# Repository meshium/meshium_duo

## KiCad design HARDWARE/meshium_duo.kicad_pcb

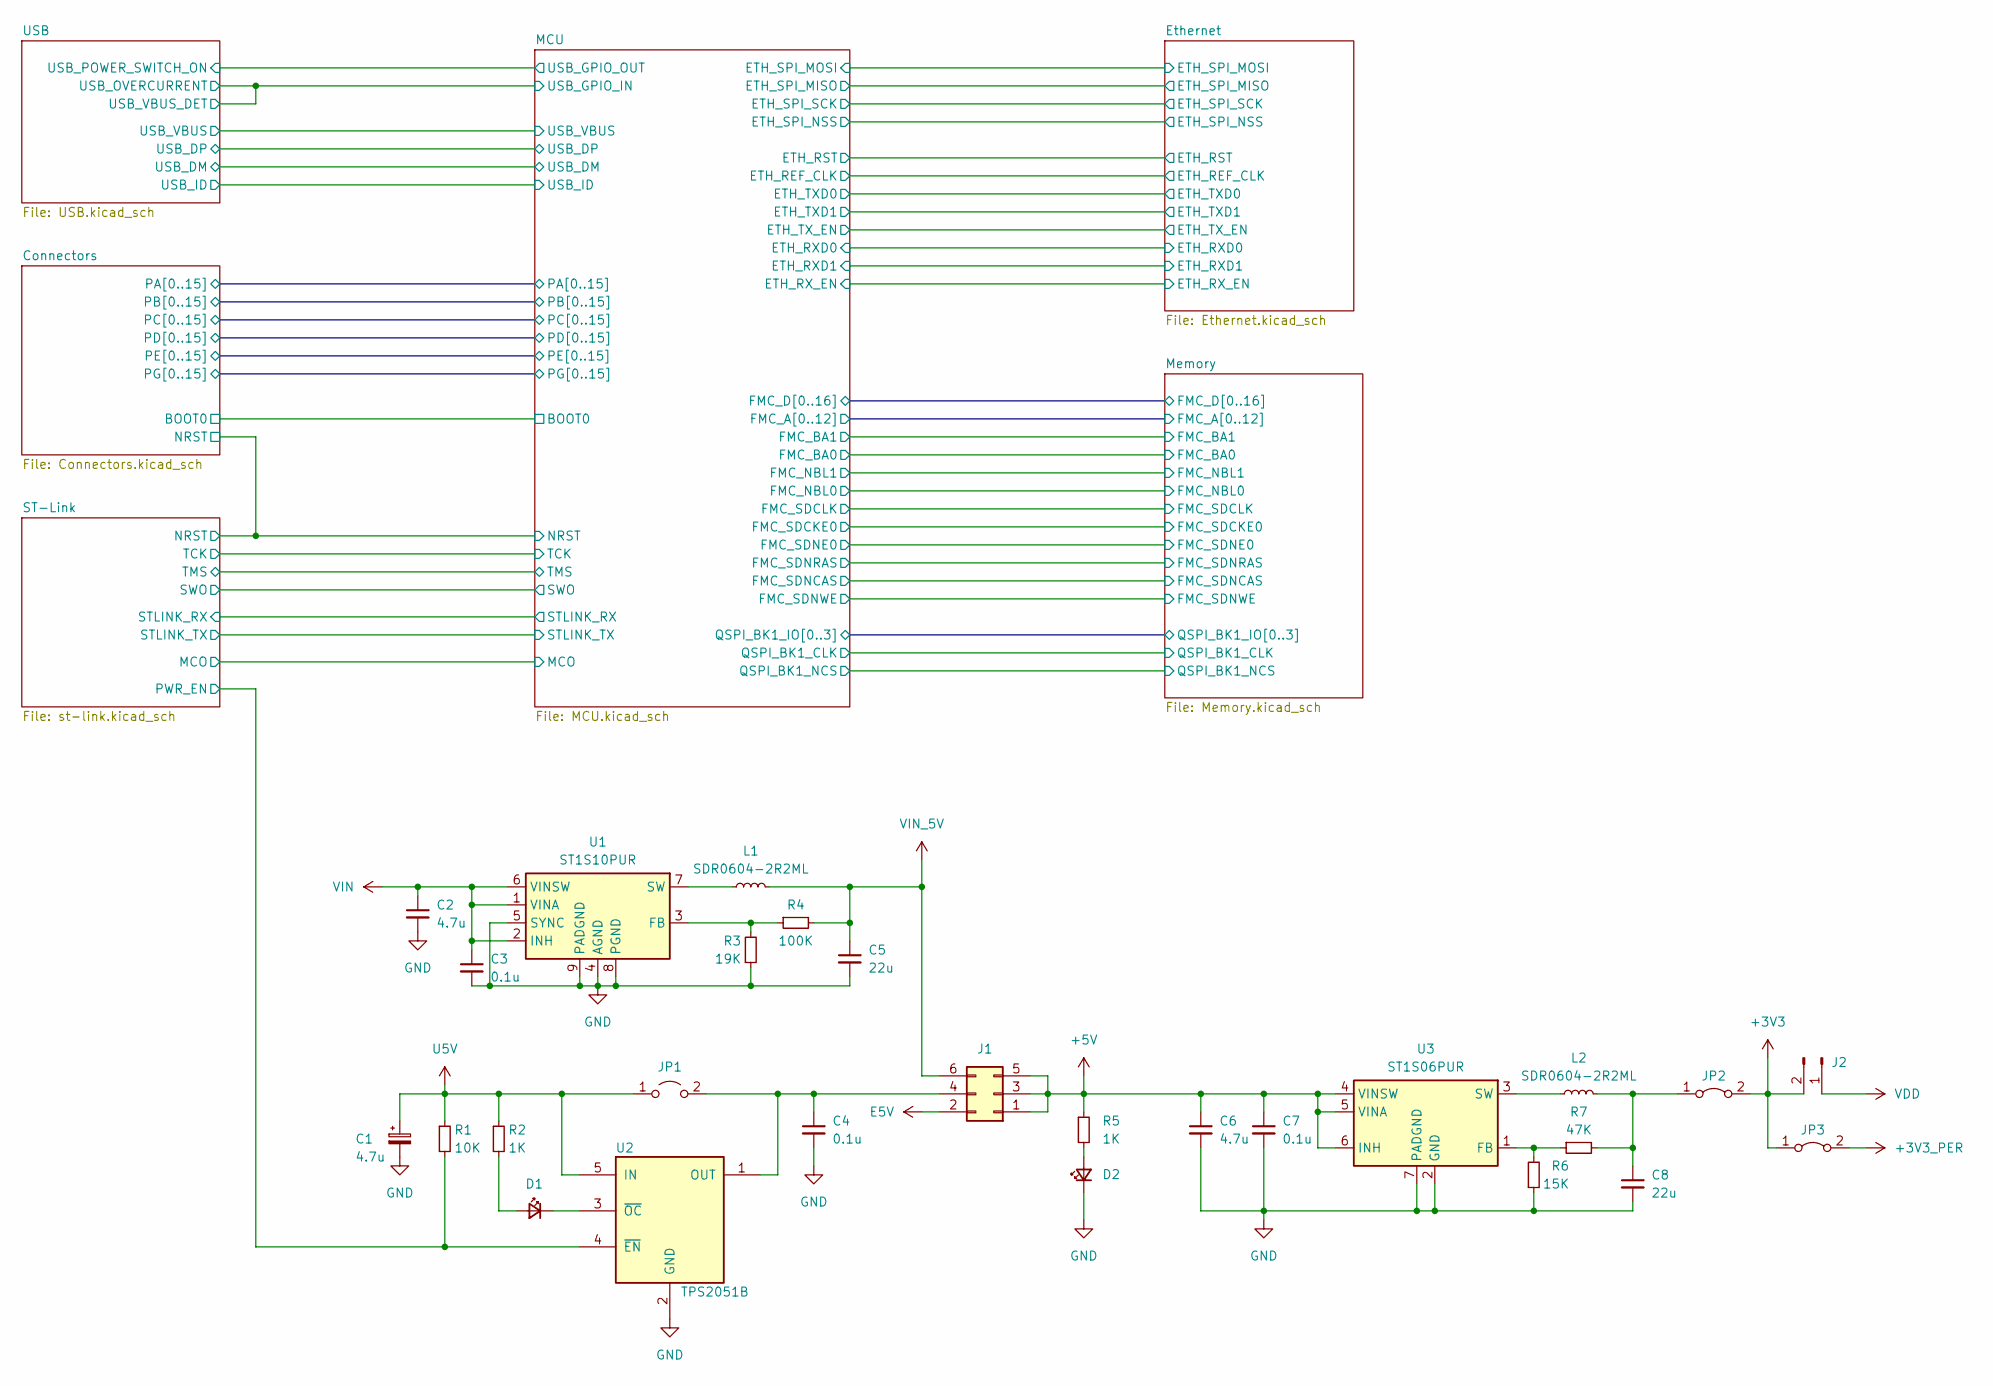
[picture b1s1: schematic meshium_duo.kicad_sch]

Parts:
C1: 4.7u; CP_EIA-6032-28_Kemet-C
C2, C6: 4.7u; C_0603_1608Metric
C3, C4, C7: 0.1u; C_0603_1608Metric
C5, C8: 22u; C_0805_2012Metric
D1, D2: LED_Small; LED_0603_1608Metric
J1: Conn_02x03_Odd_Even; PinHeader_2x03_P2.54mm_Vertical
J2: Conn_01x02_Pin; PinHeader_1x02_P2.54mm_Vertical
JP1: Jumper_2_Open; SolderJumper-2_P1.3mm_Open_TrianglePad1.0x1.5mm
JP2, JP3: Jumper_2_Bridged; SolderJumper-2_P1.3mm_Open_TrianglePad1.0x1.5mm
L1, L2: SDR0604-2R2ML; L_Bourns-SRN0604
R1: 10K; R_0603_1608Metric
R2, R5: 1K; R_0603_1608Metric
R3: 19K; R_0603_1608Metric
R4: 100K; R_0603_1608Metric
R6: 15K; R_0603_1608Metric
R7: 47K; R_0603_1608Metric
U1: ST1S10PUR; DFN-8-1EP_4x4mm_P0.8mm_EP2.5x3.6mm
U2: TPS2051B; SOT-23-5
U3: ST1S06PUR; DFN-6-1EP_3x3mm_P0.95mm_EP1.7x2.6mm

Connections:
+3V3_PER: JP3.2 (B); also elsewhere on the board
+5V: C6.1, C7.1, J1.1, J1.3, J1.5, R5.1, U3.4 (VINSW), U3.5 (VINA), U3.6 (INH); also elsewhere on the board
/ST-Link/PWR_EN: R1.2, U2.4 (~EN); also elsewhere on the board
E5V: J1.2; also elsewhere on the board
unnamed: D1.2 (A), R2.2
unnamed: D1.1 (K), U2.3 (~OC)
unnamed: D2.2 (A), R5.2
unnamed: C4.1, J1.4, JP1.2 (B), U2.1 (OUT)
unnamed: C8.1, JP2.1 (A), L2.2, R7.2
unnamed: R3.2, R4.1, U1.3 (FB)
unnamed: L1.1, U1.7 (SW)
unnamed: R6.2, R7.1, U3.1 (FB)
unnamed: L2.1, U3.3 (SW)
U5V: C1.1, JP1.1 (A), R1.1, R2.1, U2.5 (IN); also elsewhere on the board
VDD: J2.1; also elsewhere on the board
VIN: C2.1, C3.1, U1.1 (VINA), U1.2 (INH), U1.6 (VINSW); also elsewhere on the board
VIN_5V: C5.1, J1.6, L1.2, R4.2; also elsewhere on the board

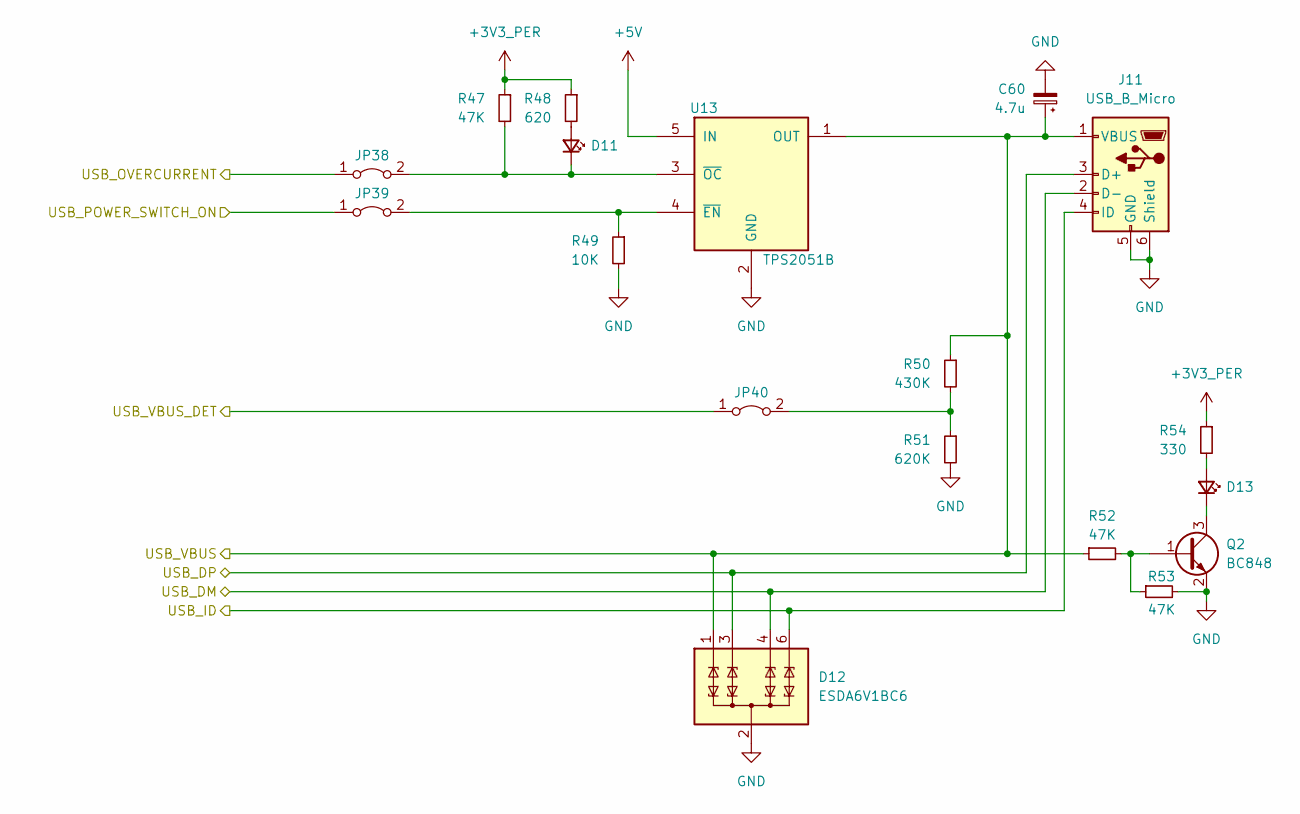
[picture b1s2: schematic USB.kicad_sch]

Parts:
C60: 4.7u; CP_EIA-6032-28_Kemet-C
D11, D13: LED_Small; LED_0603_1608Metric
D12: ESDA6V1BC6; SOT-23-6
J11: USB_B_Micro; USB_Micro-B_CUZD188-CB1Z
JP38, JP39, JP40: Jumper_2_Bridged; SolderJumper-2_P1.3mm_Open_TrianglePad1.0x1.5mm
Q2: BC848; SOT-23
R47, R52, R53: 47K; R_0603_1608Metric
R48: 620; R_0603_1608Metric
R49: 10K; R_0603_1608Metric
R50: 430K; R_0603_1608Metric
R51: 620K; R_0603_1608Metric
R54: 330; R_0603_1608Metric
U13: TPS2051B; SOT-23-5

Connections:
+3V3_PER: R47.1, R48.1, R54.1; also elsewhere on the board
+5V: U13.5 (IN); also elsewhere on the board
/Connectors/PG6: JP39.1 (A); also elsewhere on the board
/MCU/USB_DM: D12.4 (TVS3), J11.2 (D-); also elsewhere on the board
/MCU/USB_DP: D12.3 (TVS2), J11.3 (D+); also elsewhere on the board
/MCU/USB_GPIO_IN: JP38.1 (A), JP40.1 (A); also elsewhere on the board
/MCU/USB_ID: D12.6 (TVS4), J11.4 (ID); also elsewhere on the board
/MCU/USB_VBUS: C60.1, D12.1 (TVS1), J11.1 (VBUS), R50.1, R52.1, U13.1 (OUT); also elsewhere on the board
unnamed: D11.2 (A), R48.2
unnamed: D11.1 (K), JP38.2 (B), R47.2, U13.3 (~OC)
unnamed: D13.2 (A), R54.2
unnamed: D13.1 (K), Q2.3 (C)
unnamed: JP39.2 (B), R49.1, U13.4 (~EN)
unnamed: JP40.2 (B), R50.2, R51.1
unnamed: Q2.1 (B), R52.2, R53.1

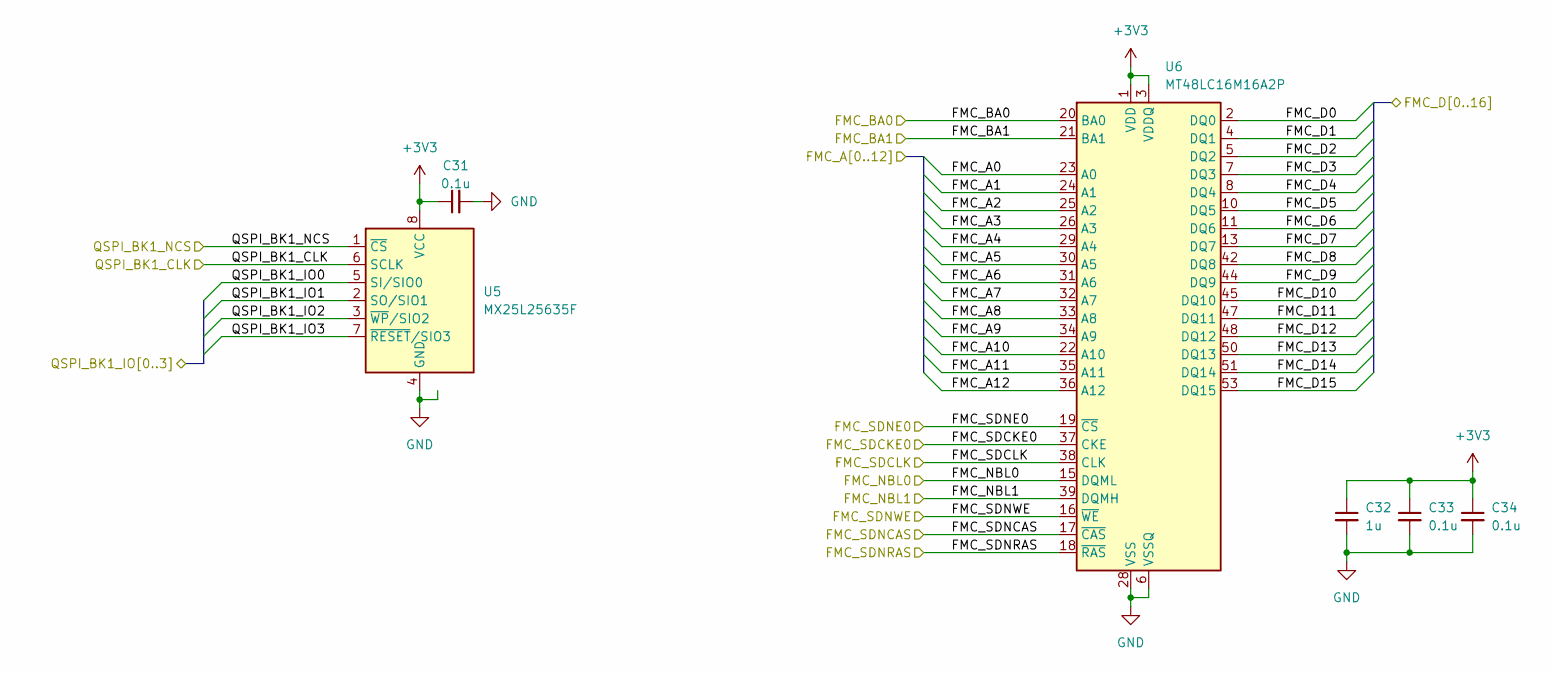
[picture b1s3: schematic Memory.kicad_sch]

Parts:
C31, C33, C34: 0.1u; C_0603_1608Metric
C32: 1u; C_0603_1608Metric
U5: MX25L25635F; WSON-8-1EP_8x6mm_P1.27mm_EP3.4x4.3mm
U6: MT48LC16M16A2P; TSOP-II-54_22.2x10.16mm_P0.8mm

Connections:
/MCU/FMC_A0: U6.23 (A0); also elsewhere on the board
/MCU/FMC_A1: U6.24 (A1); also elsewhere on the board
/MCU/FMC_A2: U6.25 (A2); also elsewhere on the board
/MCU/FMC_A3: U6.26 (A3); also elsewhere on the board
/MCU/FMC_A4: U6.29 (A4); also elsewhere on the board
/MCU/FMC_A5: U6.30 (A5); also elsewhere on the board
/MCU/FMC_A6: U6.31 (A6); also elsewhere on the board
/MCU/FMC_A7: U6.32 (A7); also elsewhere on the board
/MCU/FMC_A8: U6.33 (A8); also elsewhere on the board
/MCU/FMC_A9: U6.34 (A9); also elsewhere on the board
/MCU/FMC_A10: U6.22 (A10); also elsewhere on the board
/MCU/FMC_A11: U6.35 (A11); also elsewhere on the board
/MCU/FMC_A12: U6.36 (A12); also elsewhere on the board
/MCU/FMC_BA0: U6.20 (BA0); also elsewhere on the board
/MCU/FMC_BA1: U6.21 (BA1); also elsewhere on the board
/MCU/FMC_D0: U6.2 (DQ0); also elsewhere on the board
/MCU/FMC_D1: U6.4 (DQ1); also elsewhere on the board
/MCU/FMC_D2: U6.5 (DQ2); also elsewhere on the board
/MCU/FMC_D3: U6.7 (DQ3); also elsewhere on the board
/MCU/FMC_D4: U6.8 (DQ4); also elsewhere on the board
/MCU/FMC_D5: U6.10 (DQ5); also elsewhere on the board
/MCU/FMC_D6: U6.11 (DQ6); also elsewhere on the board
/MCU/FMC_D7: U6.13 (DQ7); also elsewhere on the board
/MCU/FMC_D8: U6.42 (DQ8); also elsewhere on the board
/MCU/FMC_D9: U6.44 (DQ9); also elsewhere on the board
/MCU/FMC_D10: U6.45 (DQ10); also elsewhere on the board
/MCU/FMC_D11: U6.47 (DQ11); also elsewhere on the board
/MCU/FMC_D12: U6.48 (DQ12); also elsewhere on the board
/MCU/FMC_D13: U6.50 (DQ13); also elsewhere on the board
/MCU/FMC_D14: U6.51 (DQ14); also elsewhere on the board
/MCU/FMC_D15: U6.53 (DQ15); also elsewhere on the board
/MCU/FMC_NBL0: U6.15 (DQML); also elsewhere on the board
/MCU/FMC_NBL1: U6.39 (DQMH); also elsewhere on the board
/MCU/FMC_SDCKE0: U6.37 (CKE); also elsewhere on the board
/MCU/FMC_SDCLK: U6.38 (CLK); also elsewhere on the board
/MCU/FMC_SDNCAS: U6.17 (~CAS); also elsewhere on the board
/MCU/FMC_SDNE0: U6.19 (~CS); also elsewhere on the board
/MCU/FMC_SDNRAS: U6.18 (~RAS); also elsewhere on the board
/MCU/FMC_SDNWE: U6.16 (~WE); also elsewhere on the board
/MCU/QSPI_BK1_CLK: U5.6 (SCLK); also elsewhere on the board
/MCU/QSPI_BK1_IO0: U5.5 (SI/SIO0); also elsewhere on the board
/MCU/QSPI_BK1_IO1: U5.2 (SO/SIO1); also elsewhere on the board
/MCU/QSPI_BK1_IO2: U5.3 (~WP/SIO2); also elsewhere on the board
/MCU/QSPI_BK1_IO3: U5.7 (~RESET/SIO3); also elsewhere on the board
/MCU/QSPI_BK1_NCS: U5.1 (~CS); also elsewhere on the board

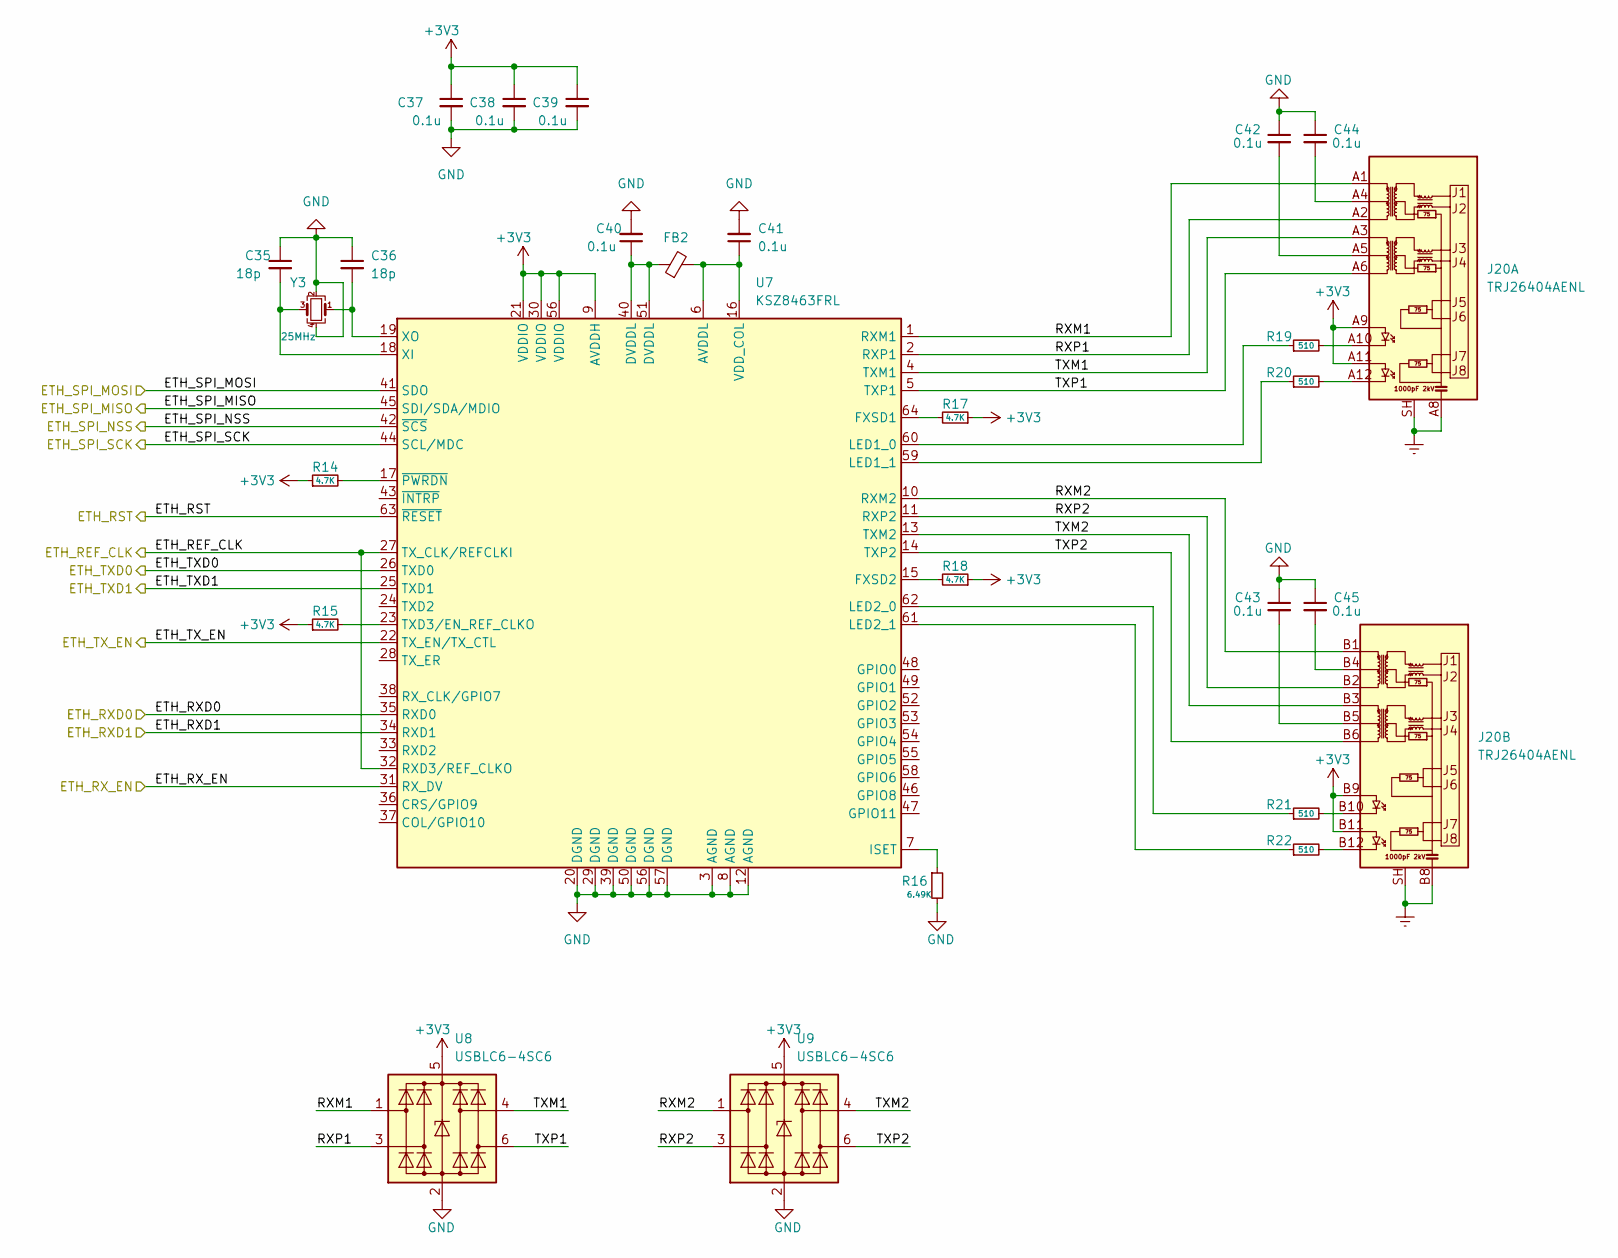
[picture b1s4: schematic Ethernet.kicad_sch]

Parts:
C35, C36: 18p; C_0603_1608Metric
C37, C38, C39, C40, C41, C42, C43, C44, C45: 0.1u; C_0603_1608Metric
FB2: FerriteBead_Small; C_0603_1608Metric
J20: TRJ26404AENL
R14, R15, R17, R18: 4.7K; R_0603_1608Metric
R16: 6.49K; R_0603_1608Metric
R19, R20, R21, R22: 510; R_0603_1608Metric
U7: KSZ8463FRL; LQFP-64_10x10mm_P0.5mm
U8, U9: USBLC6-4SC6; SOT-23-6
Y3: 25MHz; Crystal_SMD_3225-4Pin_3.2x2.5mm

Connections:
/Ethernet/ETH_REF_CLK: U7.27 (TX_CLK/REFCLKI), U7.32 (RXD3/REF_CLKO); also elsewhere on the board
/Ethernet/ETH_RST: U7.63 (~RESET)
/Ethernet/ETH_RXD0: U7.35 (RXD0); also elsewhere on the board
/Ethernet/ETH_RXD1: U7.34 (RXD1); also elsewhere on the board
/Ethernet/ETH_RX_EN: U7.31 (RX_DV); also elsewhere on the board
/Ethernet/ETH_SPI_MISO: U7.45 (SDI/SDA/MDIO); also elsewhere on the board
/Ethernet/ETH_SPI_MOSI: U7.41 (SDO); also elsewhere on the board
/Ethernet/ETH_SPI_NSS: U7.42 (~SCS); also elsewhere on the board
/Ethernet/ETH_SPI_SCK: U7.44 (SCL/MDC); also elsewhere on the board
/Ethernet/ETH_TXD0: U7.26 (TXD0); also elsewhere on the board
/Ethernet/ETH_TXD1: U7.25 (TXD1); also elsewhere on the board
/Ethernet/ETH_TX_EN: U7.22 (TX_EN/TX_CTL); also elsewhere on the board
/Ethernet/RXM1: J20.A1 (RD+), U7.1 (RXM1), U8.1 (I/O1)
/Ethernet/RXM2: J20.B1 (RD+), U7.10 (RXM2), U9.1 (I/O1)
/Ethernet/RXP1: J20.A2 (RD-), U7.2 (RXP1), U8.3 (I/O2)
/Ethernet/RXP2: J20.B2 (RD-), U7.11 (RXP2), U9.3 (I/O2)
/Ethernet/TXM1: J20.A3 (TD+), U7.4 (TXM1), U8.4 (I/O3)
/Ethernet/TXM2: J20.B3 (TD+), U7.13 (TXM2), U9.4 (I/O3)
/Ethernet/TXP1: J20.A6 (TD-), U7.5 (TXP1), U8.6 (I/O4)
/Ethernet/TXP2: J20.B6 (TD-), U7.14 (TXP2), U9.6 (I/O4)
unnamed: C40.1, FB2.1, U7.40 (DVDDL), U7.51 (DVDDL)
unnamed: C42.2, J20.A5 (CT)
unnamed: C43.2, J20.B5 (CT)
unnamed: C44.2, J20.A4 (CT)
unnamed: C45.2, J20.B4 (CT)
unnamed: J20.A8 (TERM), J20.B8 (TERM), J20.SH (SHIELD)
unnamed: J20.A10 (LEDG_C), R19.2
unnamed: J20.A12 (LEDY_C), R20.2
unnamed: J20.B10 (LEDG_C), R21.2
unnamed: J20.B12 (LEDY_C), R22.2
unnamed: C41.1, FB2.2, U7.6 (AVDDL), U7.16 (VDD_COL)
unnamed: R17.2, U7.64 (FXSD1)
unnamed: R18.2, U7.15 (FXSD2)
unnamed: R16.1, U7.7 (ISET)
unnamed: R19.1, U7.60 (LED1_0)
unnamed: R20.1, U7.59 (LED1_1)
unnamed: R21.1, U7.62 (LED2_0)
unnamed: R22.1, U7.61 (LED2_1)
unnamed: R15.2, U7.23 (TXD3/EN_REF_CLKO)
unnamed: C35.2, U7.18 (XI), Y3.3
unnamed: C36.2, U7.19 (XO), Y3.1
unnamed: R14.2, U7.17 (~PWRDN)

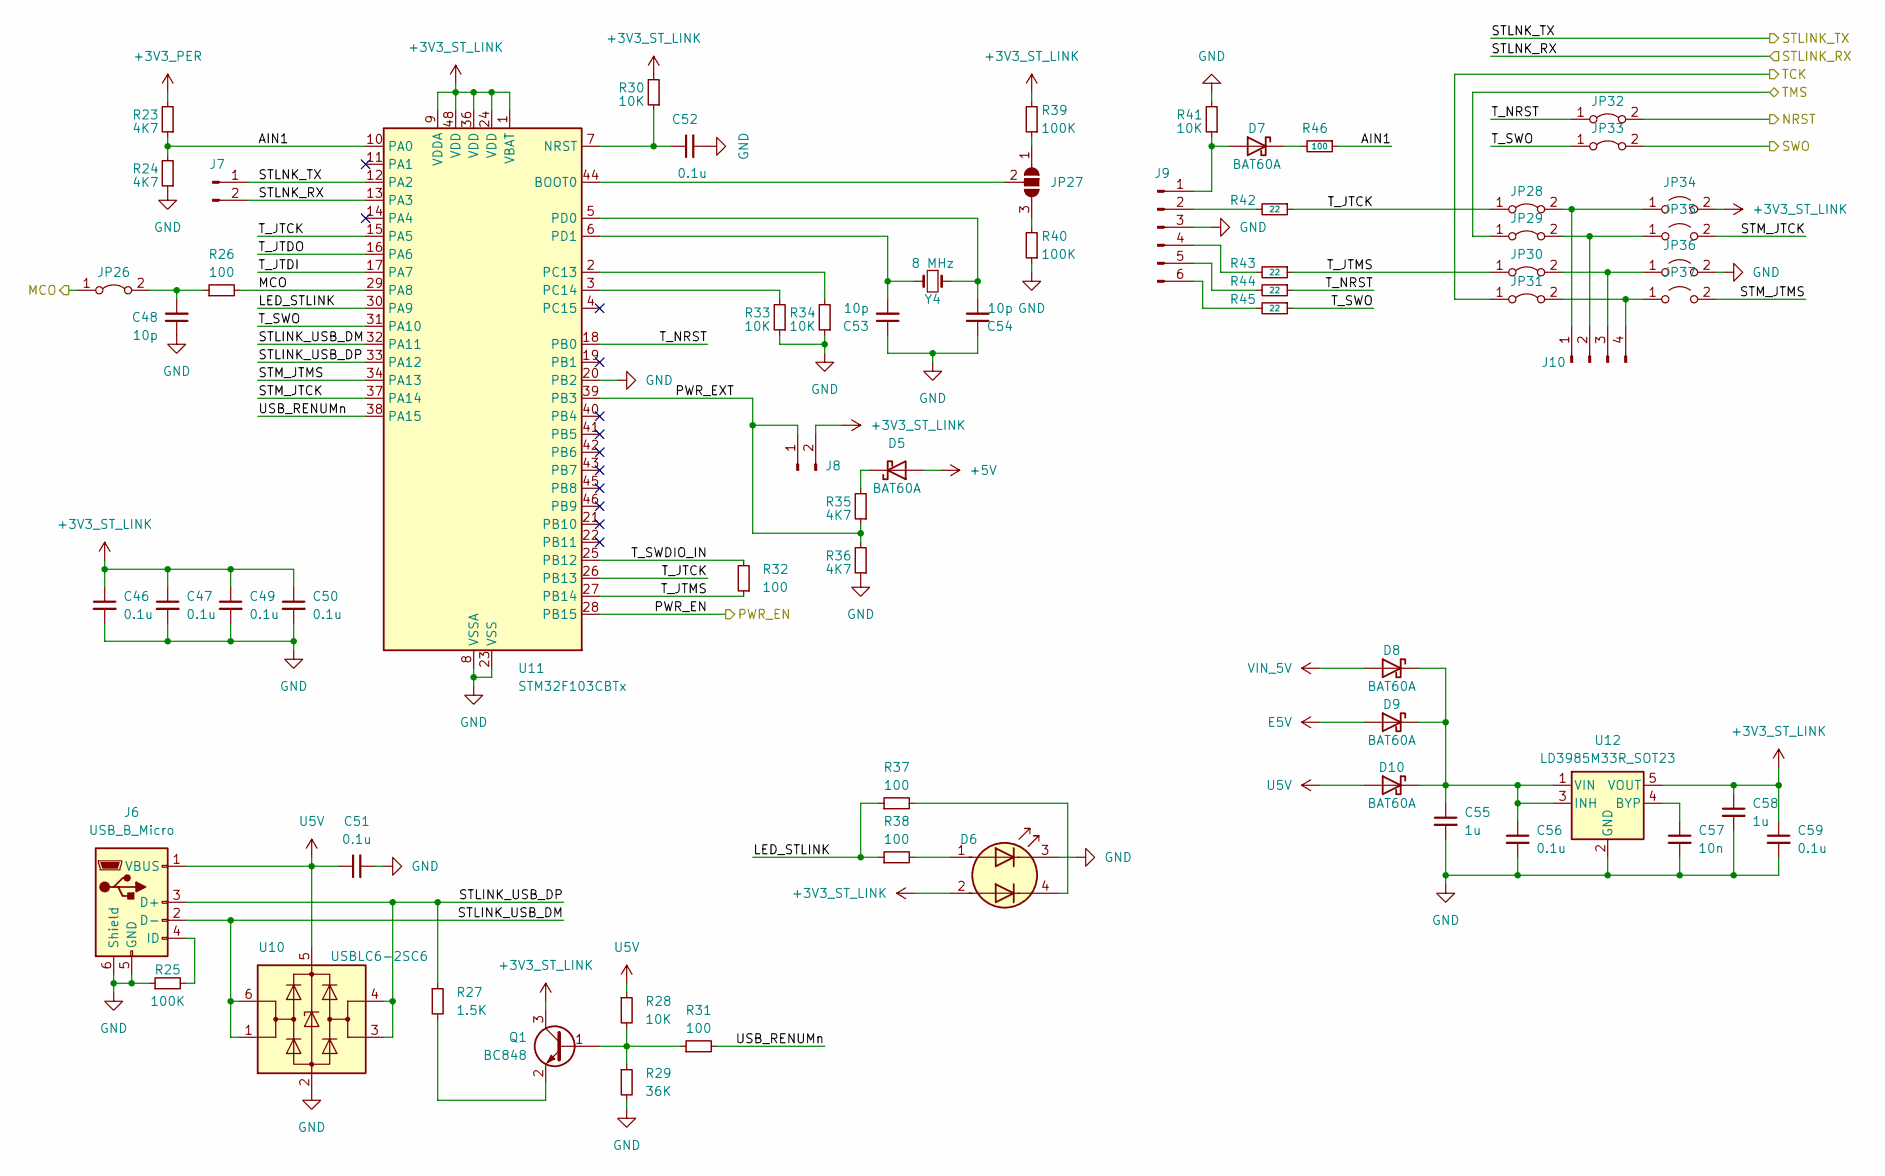
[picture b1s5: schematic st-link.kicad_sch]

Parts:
C46, C47, C49, C50, C51, C52, C56, C59: 0.1u; C_0603_1608Metric
C48, C53, C54: 10p; C_0603_1608Metric
C55, C58: 1u; C_0603_1608Metric
C57: 10n; C_0603_1608Metric
D5, D7, D8, D9, D10: BAT60A; D_SOD-323
D6: LED_Dual_AAKK; LED_Kingbright_KPBD-3224
J6: USB_B_Micro; USB_Micro-B_CUZD188-CB1Z
J7, J8: Conn_01x02_Pin; PinHeader_1x02_P2.54mm_Vertical
J9: Conn_01x06_Pin; PinHeader_1x06_P2.54mm_Vertical
J10: Conn_01x04_Pin; PinHeader_1x04_P2.54mm_Vertical
JP26, JP28, JP29, JP30, JP31, JP32, JP33: Jumper_2_Bridged; SolderJumper-2_P1.3mm_Open_TrianglePad1.0x1.5mm
JP27: SolderJumper_3_Open; SolderJumper-3_P2.0mm_Open_TrianglePad1.0x1.5mm_NumberLabels
JP34, JP35, JP36, JP37: Jumper_2_Open; SolderJumper-2_P1.3mm_Open_TrianglePad1.0x1.5mm
Q1: BC848; SOT-23
R23, R24, R35, R36: 4K7; R_0603_1608Metric
R25, R39, R40: 100K; R_0603_1608Metric
R26, R31, R32, R37, R38, R46: 100; R_0603_1608Metric
R27: 1.5K; R_0603_1608Metric
R28, R30, R33, R34, R41: 10K; R_0603_1608Metric
R29: 36K; R_0603_1608Metric
R42, R43, R44, R45: 22; R_0603_1608Metric
U10: USBLC6-2SC6; SOT-23-6
U11: STM32F103CBTx; LQFP-48_7x7mm_P0.5mm
U12: LD3985M33R_SOT23; SOT-23-5
Y4: 8 MHz; Crystal_SMD_3225-4Pin_3.2x2.5mm

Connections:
+3V3_PER: R23.2; also elsewhere on the board
+3V3_ST_LINK: C46.1, C47.1, C49.1, C50.1, C58.1, C59.1, D6.2 (A2), J8.2, JP34.2 (B), Q1.3 (C), R30.2, R39.2, U11.1 (VBAT), U11.9 (VDDA), U11.24 (VDD), U11.36 (VDD), U11.48 (VDD), U12.5 (VOUT)
+5V: D5.2 (A); also elsewhere on the board
/Connectors/NRST: JP32.2 (B); also elsewhere on the board
/MCU/MCO: JP26.1 (A), R26.2, U11.29 (PA8); also elsewhere on the board
/MCU/SWO: JP33.2 (B); also elsewhere on the board
/MCU/TCK: JP31.1 (A); also elsewhere on the board
/MCU/TMS: JP29.1 (A); also elsewhere on the board
/MCU/USART3_RX: J7.1, U11.12 (PA2); also elsewhere on the board
/MCU/USART3_TX: J7.2, U11.13 (PA3); also elsewhere on the board
/ST-Link/AIN1: R23.1, R24.2, R46.1, U11.10 (PA0)
/ST-Link/LED_STLINK: R37.1, R38.1, U11.30 (PA9)
/ST-Link/PWR_EN: U11.28 (PB15); also elsewhere on the board
/ST-Link/PWR_EXT: J8.1, R35.1, R36.2, U11.39 (PB3)
/ST-Link/STLINK_USB_DM: J6.2 (D-), U10.1 (I/O1), U10.6 (I/O1), U11.32 (PA11)
/ST-Link/STLINK_USB_DP: J6.3 (D+), R27.1, U10.3 (I/O2), U10.4 (I/O2), U11.33 (PA12)
/ST-Link/STM_JTCK: JP35.2 (B), U11.37 (PA14)
/ST-Link/STM_JTMS: JP37.2 (B), U11.34 (PA13)
/ST-Link/T_JTCK: JP28.1 (A), R42.1, U11.15 (PA5), U11.26 (PB13)
/ST-Link/T_JTDI: U11.17 (PA7)
/ST-Link/T_JTDO: U11.16 (PA6)
/ST-Link/T_JTMS: JP30.1 (A), R32.1, R43.1, U11.27 (PB14)
/ST-Link/T_NRST: JP32.1 (A), R44.1, U11.18 (PB0)
/ST-Link/T_SWDIO_IN: R32.2, U11.25 (PB12)
/ST-Link/T_SWO: JP33.1 (A), R45.1, U11.31 (PA10)
/ST-Link/USB_RENUMn: R31.2, U11.38 (PA15)
E5V: D9.2 (A); also elsewhere on the board
unnamed: D5.1 (K), R35.2
unnamed: D6.1 (A1), R38.2
unnamed: D6.4 (K2), R37.2
unnamed: D7.2 (A), J9.1, R41.1
unnamed: D7.1 (K), R46.2
unnamed: C55.1, C56.1, D8.1 (K), D9.1 (K), D10.1 (K), U12.1 (VIN), U12.3 (INH)
unnamed: J6.4 (ID), R25.2
unnamed: J9.2, R42.2
unnamed: J9.4, R43.2
unnamed: J9.5, R44.2
unnamed: J9.6, R45.2
unnamed: J10.1, JP28.2 (B), JP34.1 (A)
unnamed: J10.2, JP29.2 (B), JP35.1 (A)
unnamed: J10.3, JP30.2 (B), JP36.1 (A)
unnamed: J10.4, JP31.2 (B), JP37.1 (A)
unnamed: C48.2, JP26.2 (B), R26.1
unnamed: JP27.1 (A), R39.1
unnamed: JP27.3 (B), R40.2
unnamed: JP27.2 (C), U11.44 (BOOT0)
unnamed: Q1.1 (B), R28.2, R29.1, R31.1
unnamed: Q1.2 (E), R27.2
unnamed: C52.1, R30.1, U11.7 (NRST)
unnamed: R34.2, U11.2 (PC13)
unnamed: R33.2, U11.3 (PC14)
unnamed: C54.2, U11.5 (PD0), Y4.1
unnamed: C53.2, U11.6 (PD1), Y4.3
unnamed: C57.1, U12.4 (BYP)
U5V: C51.1, D10.2 (A), J6.1 (VBUS), R28.1, U10.5 (VBUS); also elsewhere on the board
VIN_5V: D8.2 (A); also elsewhere on the board
